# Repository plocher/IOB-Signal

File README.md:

# IOB-Signal
## License: CERN Open Hardware Licence v1.2

IOB Interface drives 2x Signal Heads via a RJ45/8 connector.

PNP Ready: IOB Signal interface for my I2C-7311 IO expansion board and a RJ45 SignalHead Adapter board.

  * pin 1: 5vDC
  * pin 2: Head1-A
  * pin 3: Head1-B
  * pin 4: Head2-A
  * pin 5: Head2-B
  * pin 6: GND

Logic - write a total of 4 bits to the desired expander nibble, 2 bits per head:

| Head1 | bit4 | bit3 | bit1 | bit0 | Indication    |
|------ |:----:|:----:|:----:|:----:|:==========    |
|       |  -   |  -   |  0   |  0   | 0b00 = GREEN  |
|------ |----- |----- |----- |----- |-----------    |
|       |  -   |  -   |  0   |  1   | 0b01 = RED    |
|------ |----- |----- |----- |----- |-----------    |
|       |  -   |  -   |  1   |  0   | 0b10 = YELLOW |
|------ |----- |----- |----- |----- |-----------    |
|       |  -   |  -   |  1   |  1   | 0b11 = DARK   |
|------ |----- |----- |----- |----- |-----------    |

| Head2 | bit4 | bit3 | bit1 | bit0 | Indication    |
|------ |:----:|:----:|:----:|:----:|:==========    |
|       |  0   |  0   |  -   |  -   | 0b00 = GREEN  |
|------ |----- |----- |----- |----- |-----------    |
|       |  0   |  1   |  -   |  -   | 0b01 = RED    |
|------ |----- |----- |----- |----- |-----------    |
|       |  1   |  0   |  -   |  -   | 0b10 = YELLOW |
|------ |----- |----- |----- |----- |-----------    |
|       |  1   |  1   |  -   |  -   | 0b11 = DARK   |
|------ |----- |----- |----- |----- |-----------    |

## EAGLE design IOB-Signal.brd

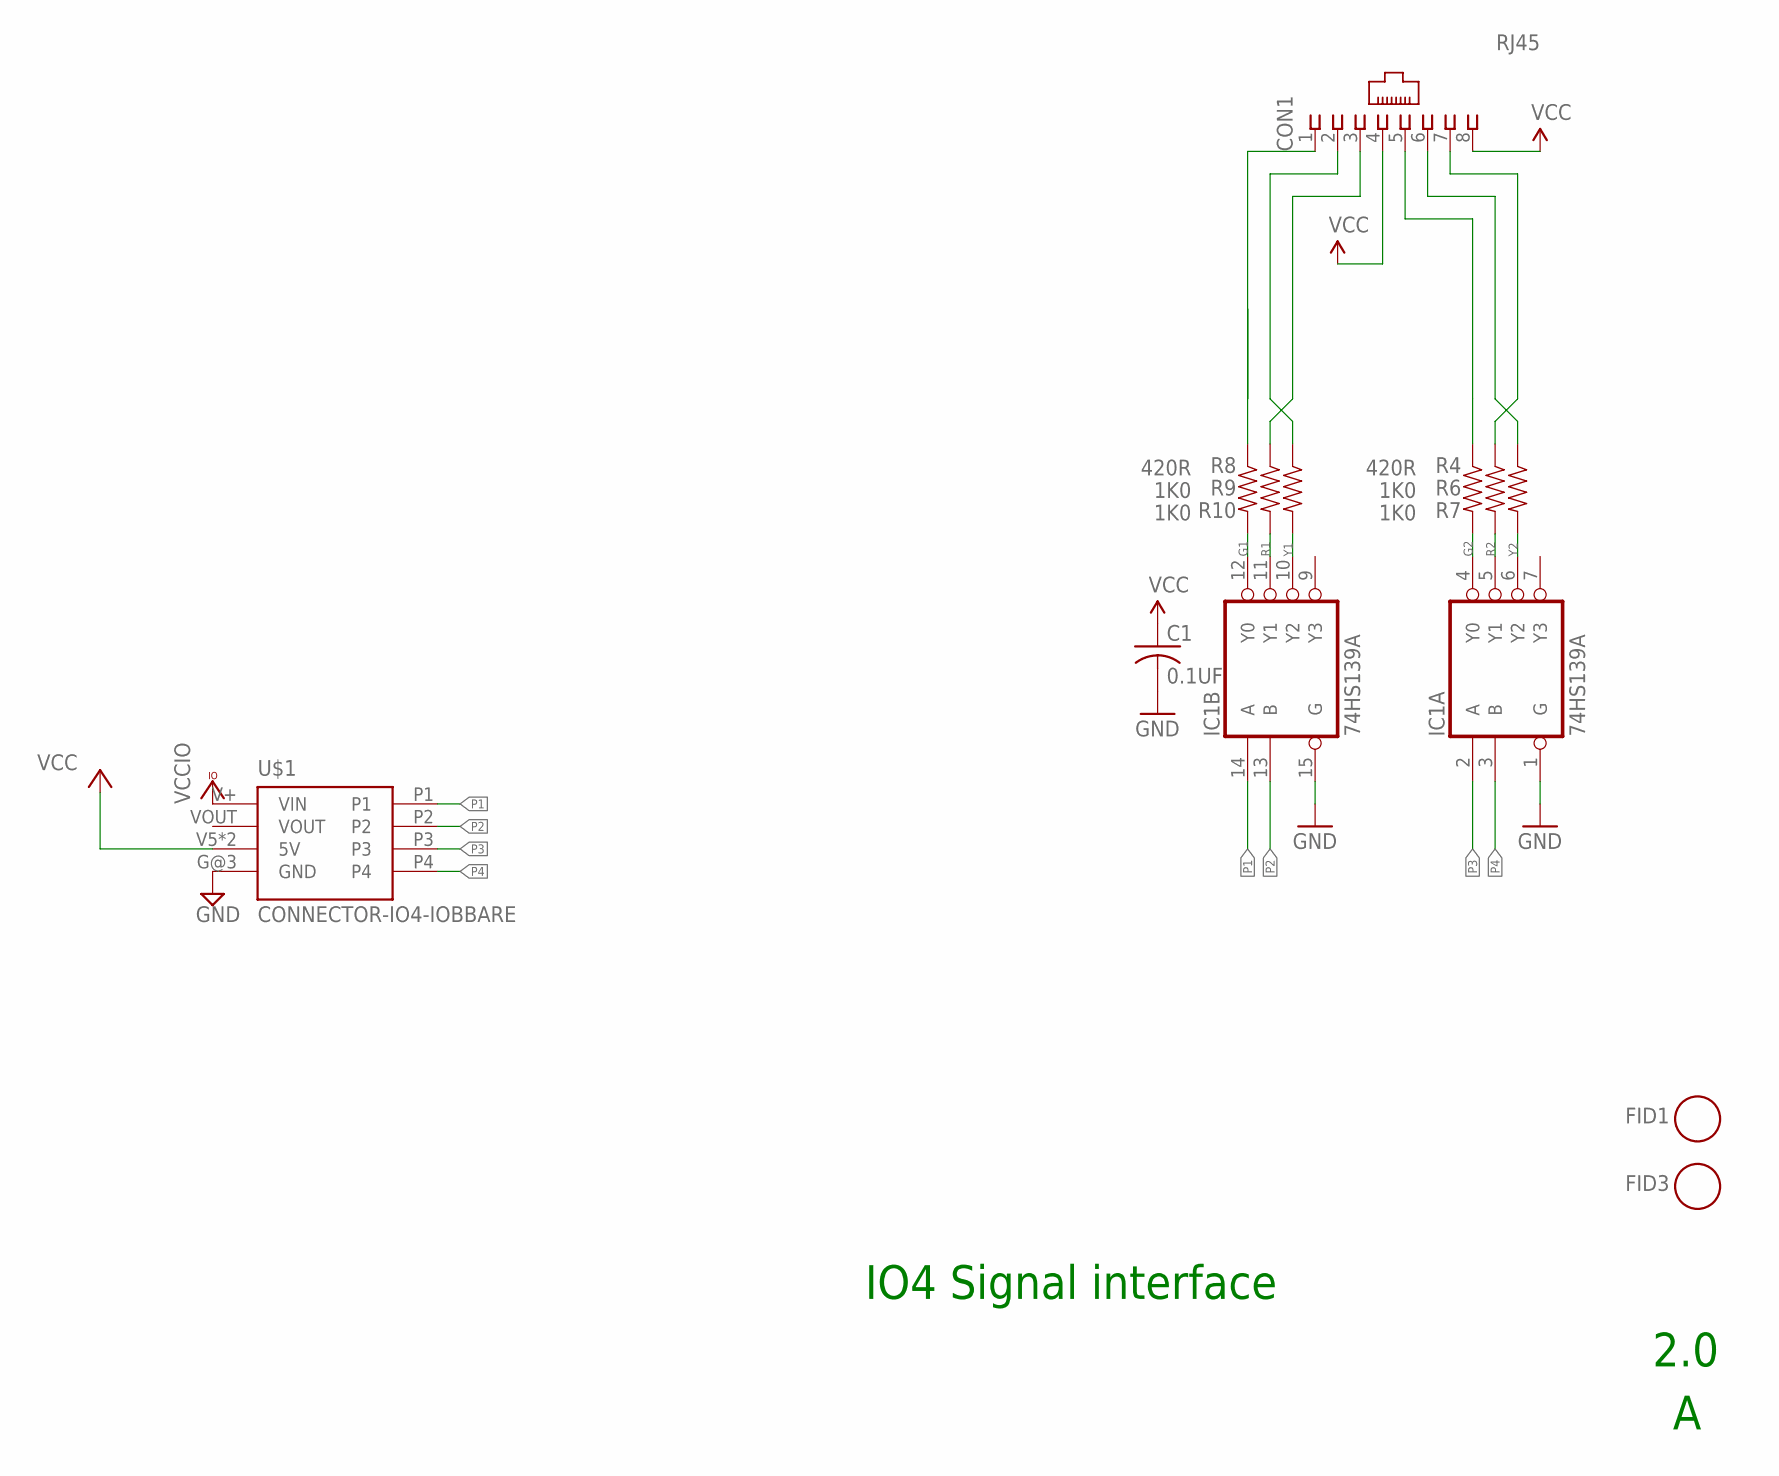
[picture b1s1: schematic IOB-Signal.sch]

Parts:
C1: 0.1UF; 0805-CAP
CON1: RJ45; RJ45-NO-SHIELD
FID1, FID3: FIDUCIAL; FIDUCIAL_1MM
IC1: 74HS139A; SO16
R4, R8: 420R; 0805-RES
R6, R7, R9, R10: 1K0; 0805-RES
U$1: CONNECTOR-IO4-IOBBARE; IO4-IOB

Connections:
G1: IC1.12 (Y0), R10.2
G1-LED: CON1.1, R10.1
G2: IC1.4 (Y0), R7.2
G2-LED: CON1.5, R7.1
GND: C1.2, IC1.1 (G), IC1.8 (GND), IC1.15 (G), U$1.G@3 (GND)
P1: IC1.14 (A), U$1.P1
P2: IC1.13 (B), U$1.P2
P3: IC1.2 (A), U$1.P3
P4: IC1.3 (B), U$1.P4
R1: IC1.11 (Y1), R9.2
R1-LED: CON1.3, R9.1
R2: IC1.5 (Y1), R6.2
R2-LED: CON1.7, R6.1
VCC: C1.1, CON1.4, CON1.8, IC1.16 (VCC), U$1.V5 (5V), U$1.V5@1 (5V)
VCCIO: U$1.V+ (VIN)
Y1: IC1.10 (Y2), R8.2
Y1-LED: CON1.2, R8.1
Y2: IC1.6 (Y2), R4.2
Y2-LED: CON1.6, R4.1

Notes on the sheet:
IO4 Signal interface
2.0

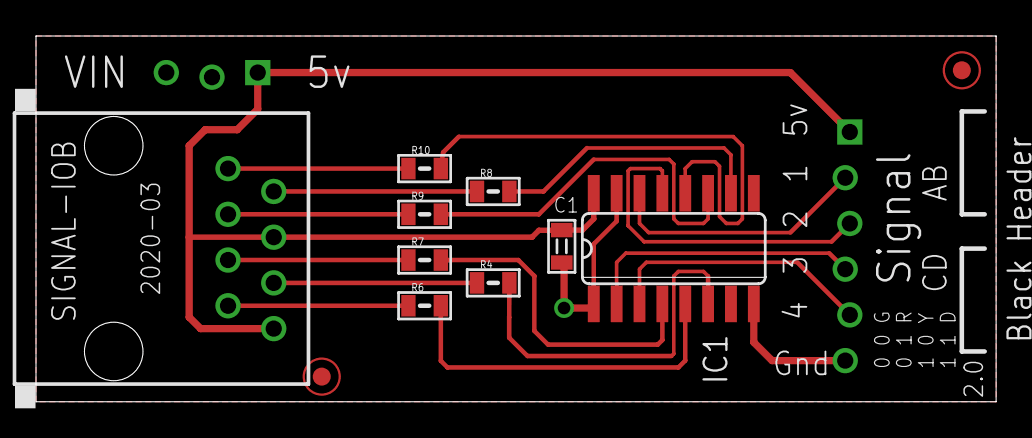
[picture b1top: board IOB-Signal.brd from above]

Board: 2 copper layers, 53.3 x 20.3 mm, 12 parts (0 on the bottom side), 18 nets.

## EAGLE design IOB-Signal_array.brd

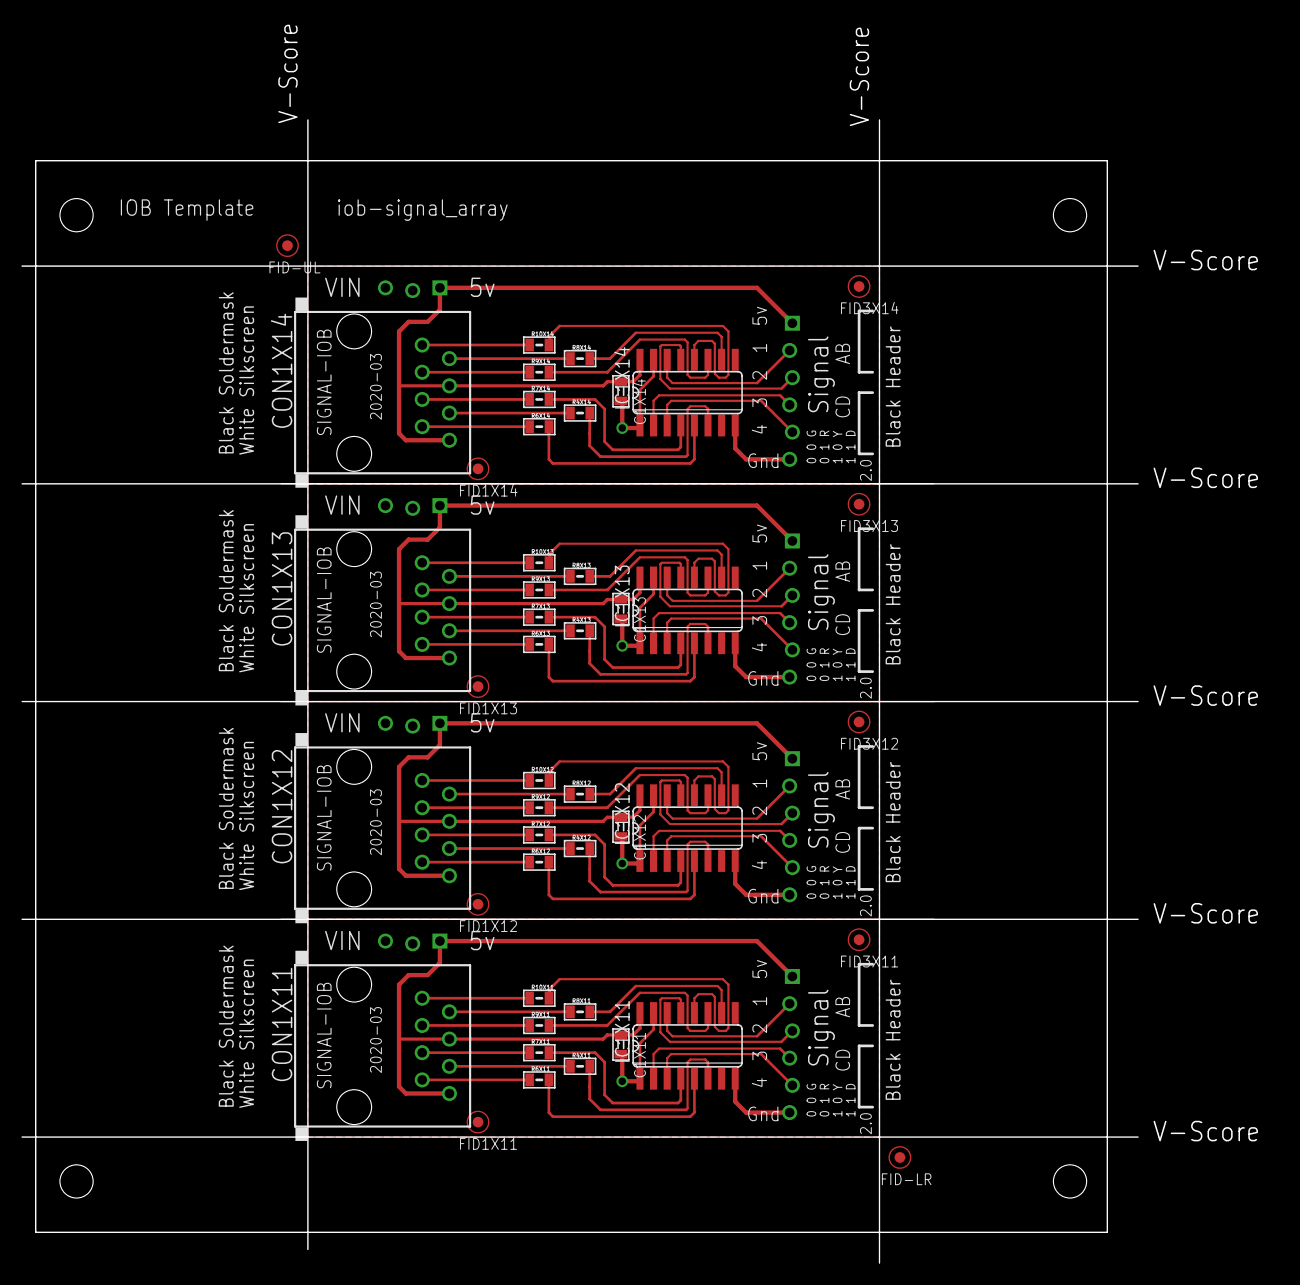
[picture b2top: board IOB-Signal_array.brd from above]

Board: 2 copper layers, 104.1 x 106.7 mm, 51 parts (0 on the bottom side), 72 nets.

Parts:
C1X11, C1X12, C1X13, C1X14: 0.1UF; 0805-CAP
CON1X11, CON1X12, CON1X13, CON1X14: RJ45; RJ45-NO-SHIELD
FID1X11, FID1X12, FID1X13, FID1X14, FID3X11, FID3X12, FID3X13, FID3X14: FIDUCIAL; FIDUCIAL_1MM
FID-LR: FIDUCIAL; FIDUCIAL_1MM
FID-UL: FIDUCIAL; FIDUCIAL_1MM
IC1X11, IC1X12, IC1X13, IC1X14: 74HS139A; SO16
R4X11, R4X12, R4X13, R4X14, R8X11, R8X12, R8X13, R8X14: 420R; 0805-RES
R6X11, R6X12, R6X13, R6X14, R7X11, R7X12, R7X13, R7X14, R9X11, R9X12, R9X13, R9X14, R10X11, R10X12, R10X13, R10X14: 1K0; 0805-RES
U$1X1: BOARD-DINRAIL-3.17IN-H4X-IOB
U$1X11, U$1X12, U$1X13, U$1X14: CONNECTOR-IO4-IOBBARE; IO4-IOB

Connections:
G1-LEDX11: CON1X11.1, R10X11.1
G1-LEDX12: CON1X12.1, R10X12.1
G1-LEDX13: CON1X13.1, R10X13.1
G1-LEDX14: CON1X14.1, R10X14.1
G1X11: IC1X11.12, R10X11.2
G1X12: IC1X12.12, R10X12.2
G1X13: IC1X13.12, R10X13.2
G1X14: IC1X14.12, R10X14.2
G2-LEDX11: CON1X11.5, R7X11.1
G2-LEDX12: CON1X12.5, R7X12.1
G2-LEDX13: CON1X13.5, R7X13.1
G2-LEDX14: CON1X14.5, R7X14.1
G2X11: IC1X11.4, R7X11.2
G2X12: IC1X12.4, R7X12.2
G2X13: IC1X13.4, R7X13.2
G2X14: IC1X14.4, R7X14.2
GNDX11: C1X11.2, IC1X11.1, IC1X11.8, IC1X11.15, U$1X11.G@3
GNDX12: C1X12.2, IC1X12.1, IC1X12.8, IC1X12.15, U$1X12.G@3
GNDX13: C1X13.2, IC1X13.1, IC1X13.8, IC1X13.15, U$1X13.G@3
GNDX14: C1X14.2, IC1X14.1, IC1X14.8, IC1X14.15, U$1X14.G@3
P1X11: IC1X11.14, U$1X11.P1
P1X12: IC1X12.14, U$1X12.P1
P1X13: IC1X13.14, U$1X13.P1
P1X14: IC1X14.14, U$1X14.P1
P2X11: IC1X11.13, U$1X11.P2
P2X12: IC1X12.13, U$1X12.P2
P2X13: IC1X13.13, U$1X13.P2
P2X14: IC1X14.13, U$1X14.P2
P3X11: IC1X11.2, U$1X11.P3
P3X12: IC1X12.2, U$1X12.P3
P3X13: IC1X13.2, U$1X13.P3
P3X14: IC1X14.2, U$1X14.P3
P4X11: IC1X11.3, U$1X11.P4
P4X12: IC1X12.3, U$1X12.P4
P4X13: IC1X13.3, U$1X13.P4
P4X14: IC1X14.3, U$1X14.P4
R1-LEDX11: CON1X11.3, R9X11.1
R1-LEDX12: CON1X12.3, R9X12.1
R1-LEDX13: CON1X13.3, R9X13.1
R1-LEDX14: CON1X14.3, R9X14.1
R1X11: IC1X11.11, R9X11.2
R1X12: IC1X12.11, R9X12.2
R1X13: IC1X13.11, R9X13.2
R1X14: IC1X14.11, R9X14.2
R2-LEDX11: CON1X11.7, R6X11.1
R2-LEDX12: CON1X12.7, R6X12.1
R2-LEDX13: CON1X13.7, R6X13.1
R2-LEDX14: CON1X14.7, R6X14.1
R2X11: IC1X11.5, R6X11.2
R2X12: IC1X12.5, R6X12.2
R2X13: IC1X13.5, R6X13.2
R2X14: IC1X14.5, R6X14.2
VCCX11: C1X11.1, CON1X11.4, CON1X11.8, IC1X11.16, U$1X11.V5, U$1X11.V5@1
VCCX12: C1X12.1, CON1X12.4, CON1X12.8, IC1X12.16, U$1X12.V5, U$1X12.V5@1
VCCX13: C1X13.1, CON1X13.4, CON1X13.8, IC1X13.16, U$1X13.V5, U$1X13.V5@1
VCCX14: C1X14.1, CON1X14.4, CON1X14.8, IC1X14.16, U$1X14.V5, U$1X14.V5@1
Y1-LEDX11: CON1X11.2, R8X11.1
Y1-LEDX12: CON1X12.2, R8X12.1
Y1-LEDX13: CON1X13.2, R8X13.1
Y1-LEDX14: CON1X14.2, R8X14.1
Y1X11: IC1X11.10, R8X11.2
Y1X12: IC1X12.10, R8X12.2
Y1X13: IC1X13.10, R8X13.2
Y1X14: IC1X14.10, R8X14.2
Y2-LEDX11: CON1X11.6, R4X11.1
Y2-LEDX12: CON1X12.6, R4X12.1
Y2-LEDX13: CON1X13.6, R4X13.1
Y2-LEDX14: CON1X14.6, R4X14.1
Y2X11: IC1X11.6, R4X11.2
Y2X12: IC1X12.6, R4X12.2
Y2X13: IC1X13.6, R4X13.2
Y2X14: IC1X14.6, R4X14.2

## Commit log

2019-12-09 added graphic
2020-03-06 new IOB format
2020-03-07 updated changelog
2020-05-04 updated tags
2020-05-04 panelized
2020-08-09 fixed SPCoast.lbr diode orientation
2020-08-09 Added missing values
2020-08-11 normalized silkscreen layout across IOBs
2020-08-11 bottom silk alignment
2020-08-12 Black soldermask
